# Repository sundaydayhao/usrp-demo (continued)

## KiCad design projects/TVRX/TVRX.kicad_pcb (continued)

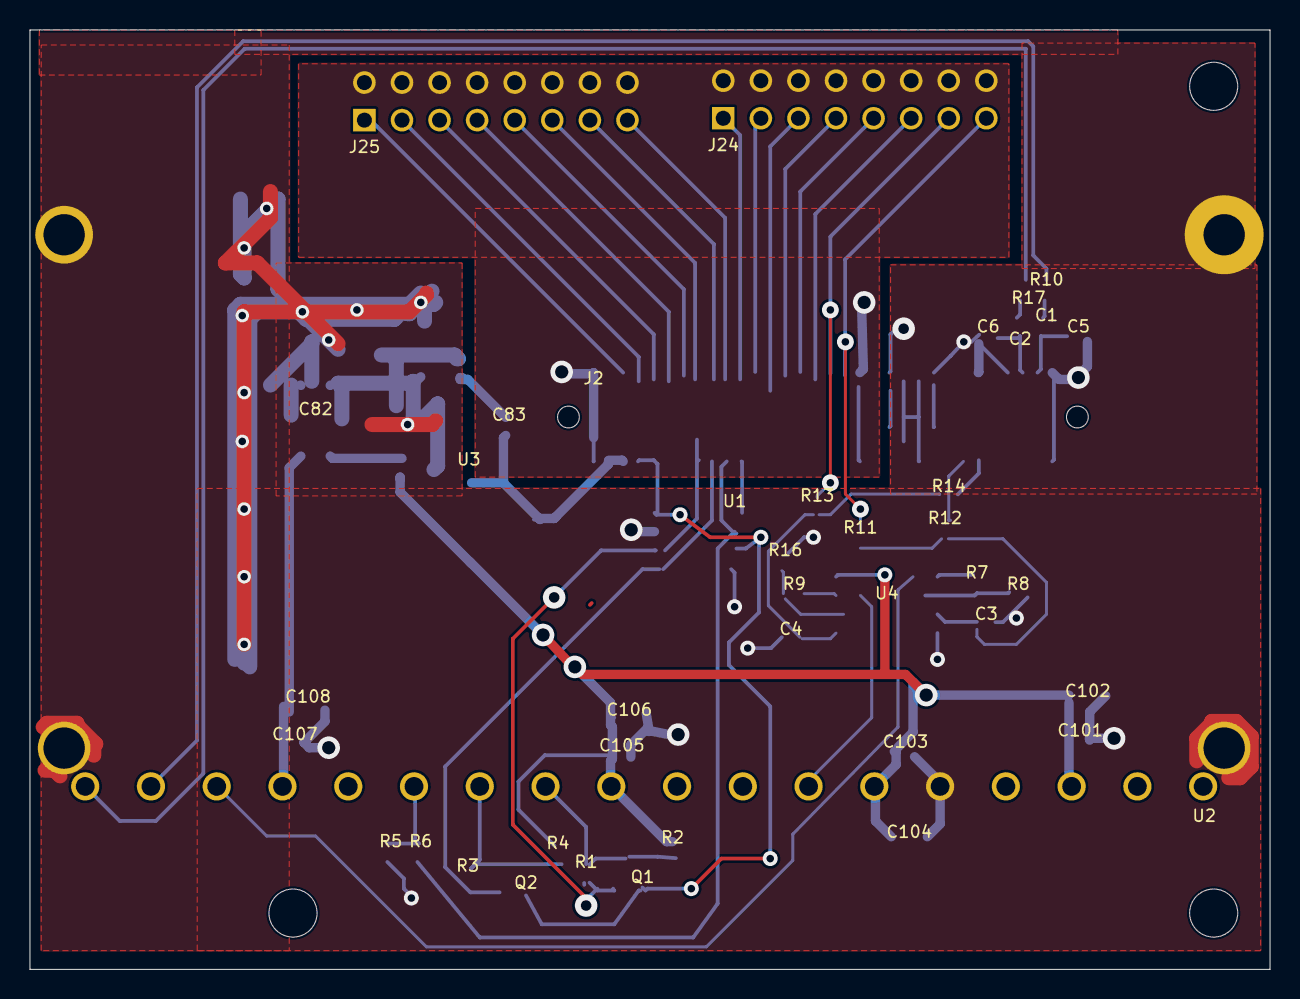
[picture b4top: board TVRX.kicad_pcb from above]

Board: 4 copper layers, 83.8 x 63.5 mm, 44 parts (0 on the bottom side), 43 nets.

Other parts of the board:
H1, H2, H3: NPTH

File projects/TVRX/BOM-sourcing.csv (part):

Reference,Value,Footprint,Manufacturer,MPN,LCSC,Sourcing_status,Specification,Source_value,Evidence,Approved_brands,Sourcing_policy
C1,.1uF,USRP:C1,候选：Murata / TDK / Samsung Electro-Mechanics / Walsin / FH / EYANG,,,规格选型，待锁定料号,按项目焊盘尺寸；RF/匹配/PLL环路优先 C0G；去耦 X7R；耐压 >=16 V；保留原容差,.1uF,,Murata / TDK / Samsung Electro-Mechanics / Walsin / FH / EYANG,国产与国际品牌均可；满足参数后比较含税到手价、起订量、库存和交期；换料须复核封装及电气指标
C2,.1uF,USRP:C2,候选：Murata / TDK / Samsung Electro-Mechanics / Walsin / FH / EYANG,,,规格选型，待锁定料号,按项目焊盘尺寸；RF/匹配/PLL环路优先 C0G；去耦 X7R；耐压 >=16 V；保留原容差,.1uF,,Murata / TDK / Samsung Electro-Mechanics / Walsin / FH / EYANG,国产与国际品牌均可；满足参数后比较含税到手价、起订量、库存和交期；换料须复核封装及电气指标
C3,.1uF,USRP:C3,候选：Murata / TDK / Samsung Electro-Mechanics / Walsin / FH / EYANG,,,规格选型，待锁定料号,按项目焊盘尺寸；RF/匹配/PLL环路优先 C0G；去耦 X7R；耐压 >=16 V；保留原容差,.1uF,,Murata / TDK / Samsung Electro-Mechanics / Walsin / FH / EYANG,国产与国际品牌均可；满足参数后比较含税到手价、起订量、库存和交期；换料须复核封装及电气指标
C4,.1uF,USRP:C4,候选：Murata / TDK / Samsung Electro-Mechanics / Walsin / FH / EYANG,,,规格选型，待锁定料号,按项目焊盘尺寸；RF/匹配/PLL环路优先 C0G；去耦 X7R；耐压 >=16 V；保留原容差,.1uF,,Murata / TDK / Samsung Electro-Mechanics / Walsin / FH / EYANG,国产与国际品牌均可；满足参数后比较含税到手价、起订量、库存和交期；换料须复核封装及电气指标
C5,10pF,USRP:C5,FH 风华高科,0603CG100J500NT,C91367,已核对目录料号，0603 时采用,0603; 10 pF; C0G; 50 V; +/-5%,10pF,https://www.lcsc.com/product-detail/C91367.html,Murata / TDK / Samsung Electro-Mechanics / Walsin / FH / EYANG,国产与国际品牌均可；满足参数后比较含税到手价、起订量、库存和交期；换料须复核封装及电气指标
C6,10pF,USRP:C6,FH 风华高科,0603CG100J500NT,C91367,已核对目录料号，0603 时采用,0603; 10 pF; C0G; 50 V; +/-5%,10pF,https://www.lcsc.com/product-detail/C91367.html,Murata / TDK / Samsung Electro-Mechanics / Walsin / FH / EYANG,国产与国际品牌均可；满足参数后比较含税到手价、起订量、库存和交期；换料须复核封装及电气指标
C82,22uF,USRP:C82,候选：Murata / TDK / Samsung Electro-Mechanics / Walsin / FH / EYANG,,,规格选型，待锁定料号,按项目焊盘尺寸；RF/匹配/PLL环路优先 C0G；去耦 X7R；耐压 >=16 V；保留原容差,22uF,,Murata / TDK / Samsung Electro-Mechanics / Walsin / FH / EYANG,国产与国际品牌均可；满足参数后比较含税到手价、起订量、库存和交期；换料须复核封装及电气指标
C83,.1uF,USRP:C83,候选：Murata / TDK / Samsung Electro-Mechanics / Walsin / FH / EYANG,,,规格选型，待锁定料号,按项目焊盘尺寸；RF/匹配/PLL环路优先 C0G；去耦 X7R；耐压 >=16 V；保留原容差,.1uF,,Murata / TDK / Samsung Electro-Mechanics / Walsin / FH / EYANG,国产与国际品牌均可；满足参数后比较含税到手价、起订量、库存和交期；换料须复核封装及电气指标
C101,470pF,USRP:C101,候选：Murata / TDK / Samsung Electro-Mechanics / Walsin / FH / EYANG,,,规格选型，待锁定料号,按项目焊盘尺寸；RF/匹配/PLL环路优先 C0G；去耦 X7R；耐压 >=16 V；保留原容差,470pF,,Murata / TDK / Samsung Electro-Mechanics / Walsin / FH / EYANG,国产与国际品牌均可；满足参数后比较含税到手价、起订量、库存和交期；换料须复核封装及电气指标
C102,4.7uF,USRP:C102,候选：Murata / TDK / Samsung Electro-Mechanics / Walsin / FH / EYANG,,,规格选型，待锁定料号,按项目焊盘尺寸；RF/匹配/PLL环路优先 C0G；去耦 X7R；耐压 >=16 V；保留原容差,4.7uF,,Murata / TDK / Samsung Electro-Mechanics / Walsin / FH / EYANG,国产与国际品牌均可；满足参数后比较含税到手价、起订量、库存和交期；换料须复核封装及电气指标
C103,470pF,USRP:C103,候选：Murata / TDK / Samsung Electro-Mechanics / Walsin / FH / EYANG,,,规格选型，待锁定料号,按项目焊盘尺寸；RF/匹配/PLL环路优先 C0G；去耦 X7R；耐压 >=16 V；保留原容差,470pF,,Murata / TDK / Samsung Electro-Mechanics / Walsin / FH / EYANG,国产与国际品牌均可；满足参数后比较含税到手价、起订量、库存和交期；换料须复核封装及电气指标
C104,4.7uF,USRP:C104,候选：Murata / TDK / Samsung Electro-Mechanics / Walsin / FH / EYANG,,,规格选型，待锁定料号,按项目焊盘尺寸；RF/匹配/PLL环路优先 C0G；去耦 X7R；耐压 >=16 V；保留原容差,4.7uF,,Murata / TDK / Samsung Electro-Mechanics / Walsin / FH / EYANG,国产与国际品牌均可；满足参数后比较含税到手价、起订量、库存和交期；换料须复核封装及电气指标
C105,470pF,USRP:C105,候选：Murata / TDK / Samsung Electro-Mechanics / Walsin / FH / EYANG,,,规格选型，待锁定料号,按项目焊盘尺寸；RF/匹配/PLL环路优先 C0G；去耦 X7R；耐压 >=16 V；保留原容差,470pF,,Murata / TDK / Samsung Electro-Mechanics / Walsin / FH / EYANG,国产与国际品牌均可；满足参数后比较含税到手价、起订量、库存和交期；换料须复核封装及电气指标
C106,4.7uF,USRP:C106,候选：Murata / TDK / Samsung Electro-Mechanics / Walsin / FH / EYANG,,,规格选型，待锁定料号,按项目焊盘尺寸；RF/匹配/PLL环路优先 C0G；去耦 X7R；耐压 >=16 V；保留原容差,4.7uF,,Murata / TDK / Samsung Electro-Mechanics / Walsin / FH / EYANG,国产与国际品牌均可；满足参数后比较含税到手价、起订量、库存和交期；换料须复核封装及电气指标
C107,470pF,USRP:C107,候选：Murata / TDK / Samsung Electro-Mechanics / Walsin / FH / EYANG,,,规格选型，待锁定料号,按项目焊盘尺寸；RF/匹配/PLL环路优先 C0G；去耦 X7R；耐压 >=16 V；保留原容差,470pF,,Murata / TDK / Samsung Electro-Mechanics / Walsin / FH / EYANG,国产与国际品牌均可；满足参数后比较含税到手价、起订量、库存和交期；换料须复核封装及电气指标
C108,4.7uF,USRP:C108,候选：Murata / TDK / Samsung Electro-Mechanics / Walsin / FH / EYANG,,,规格选型，待锁定料号,按项目焊盘尺寸；RF/匹配/PLL环路优先 C0G；去耦 X7R；耐压 >=16 V；保留原容差,4.7uF,,Murata / TDK / Samsung Electro-Mechanics / Walsin / FH / EYANG,国产与国际品牌均可；满足参数后比较含税到手价、起订量、库存和交期；换料须复核封装及电气指标
J2,PMC64,USRP:J2,,,,规格选型，待锁定料号,按工程封装和 USRP1 接口核对插合方向、针脚与高度,PMC64,,,
J24,HEADER16,USRP:J24,,,,规格选型，待锁定料号,按工程封装和 USRP1 接口核对插合方向、针脚与高度,HEADER16,,,
J25,HEADER16,USRP:J25,,,,规格选型，待锁定料号,按工程封装和 USRP1 接口核对插合方向、针脚与高度,HEADER16,,,
Q1,NDS355AN,USRP:Q1,,NDS355AN,,保留原功能型号；采购需核对后缀、封装与供应状态,射频/高速/低噪声器件，不作未经验证的国产等效替换,NMOS_TRANSISTOR,,,
Q2,NDS355AN,USRP:Q2,,NDS355AN,,保留原功能型号；采购需核对后缀、封装与供应状态,射频/高速/低噪声器件，不作未经验证的国产等效替换,NMOS_TRANSISTOR,,,
R1,NONE,USRP:R1,,,,DNP 不装,保留调试/选配焊盘,NONE,,,
R2,2.2K,USRP:R2,候选：YAGEO / Vishay / Panasonic / UNI-ROYAL / FH,,,规格选型，待锁定料号,0603; <=1%; >=0.1 W; 按原值采购；反馈/终端电阻需同批次,2.2K,,YAGEO / Vishay / Panasonic / UNI-ROYAL / FH,国产与国际品牌均可；满足参数后比较含税到手价、起订量、库存和交期；换料须复核封装及电气指标
R3,NONE,USRP:R3,,,,DNP 不装,保留调试/选配焊盘,NONE,,,
R4,2.2K,USRP:R4,候选：YAGEO / Vishay / Panasonic / UNI-ROYAL / FH,,,规格选型，待锁定料号,0603; <=1%; >=0.1 W; 按原值采购；反馈/终端电阻需同批次,2.2K,,YAGEO / Vishay / Panasonic / UNI-ROYAL / FH,国产与国际品牌均可；满足参数后比较含税到手价、起订量、库存和交期；换料须复核封装及电气指标
R5,1K,USRP:R5,候选：YAGEO / Vishay / Panasonic / UNI-ROYAL / FH,,,规格选型，待锁定料号,0603; <=1%; >=0.1 W; 按原值采购；反馈/终端电阻需同批次,1K,,YAGEO / Vishay / Panasonic / UNI-ROYAL / FH,国产与国际品牌均可；满足参数后比较含税到手价、起订量、库存和交期；换料须复核封装及电气指标
R6,1.6K,USRP:R6,候选：YAGEO / Vishay / Panasonic / UNI-ROYAL / FH,,,规格选型，待锁定料号,0603; <=1%; >=0.1 W; 按原值采购；反馈/终端电阻需同批次,1.6K,,YAGEO / Vishay / Panasonic / UNI-ROYAL / FH,国产与国际品牌均可；满足参数后比较含税到手价、起订量、库存和交期；换料须复核封装及电气指标
R7,2.2K,USRP:R7,候选：YAGEO / Vishay / Panasonic / UNI-ROYAL / FH,,,规格选型，待锁定料号,0603; <=1%; >=0.1 W; 按原值采购；反馈/终端电阻需同批次,2.2K,,YAGEO / Vishay / Panasonic / UNI-ROYAL / FH,国产与国际品牌均可；满足参数后比较含税到手价、起订量、库存和交期；换料须复核封装及电气指标
R8,10K,USRP:R8,候选：YAGEO / Vishay / Panasonic / UNI-ROYAL / FH,,,规格选型，待锁定料号,0603; <=1%; >=0.1 W; 按原值采购；反馈/终端电阻需同批次,10K,,YAGEO / Vishay / Panasonic / UNI-ROYAL / FH,国产与国际品牌均可；满足参数后比较含税到手价、起订量、库存和交期；换料须复核封装及电气指标
R9,2.2K,USRP:R9,候选：YAGEO / Vishay / Panasonic / UNI-ROYAL / FH,,,规格选型，待锁定料号,0603; <=1%; >=0.1 W; 按原值采购；反馈/终端电阻需同批次,2.2K,,YAGEO / Vishay / Panasonic / UNI-ROYAL / FH,国产与国际品牌均可；满足参数后比较含税到手价、起订量、库存和交期；换料须复核封装及电气指标
R10,0,USRP:R10,UNI-ROYAL 厚声,0603WAF0000T5E,C21189,已核对目录料号,0603; <=1%; >=0.1 W; 按原值采购；反馈/终端电阻需同批次,0,https://www.lcsc.com/product-detail/C21189.html,YAGEO / Vishay / Panasonic / UNI-ROYAL / FH,国产与国际品牌均可；满足参数后比较含税到手价、起订量、库存和交期；换料须复核封装及电气指标
R11,NONE,USRP:R11,,,,DNP 不装,保留调试/选配焊盘,NONE,,,
R12,10K,USRP:R12,候选：YAGEO / Vishay / Panasonic / UNI-ROYAL / FH,,,规格选型，待锁定料号,0603; <=1%; >=0.1 W; 按原值采购；反馈/终端电阻需同批次,10K,,YAGEO / Vishay / Panasonic / UNI-ROYAL / FH,国产与国际品牌均可；满足参数后比较含税到手价、起订量、库存和交期；换料须复核封装及电气指标
R13,NONE,USRP:R13,,,,DNP 不装,保留调试/选配焊盘,NONE,,,
R14,10K,USRP:R14,候选：YAGEO / Vishay / Panasonic / UNI-ROYAL / FH,,,规格选型，待锁定料号,0603; <=1%; >=0.1 W; 按原值采购；反馈/终端电阻需同批次,10K,,YAGEO / Vishay / Panasonic / UNI-ROYAL / FH,国产与国际品牌均可；满足参数后比较含税到手价、起订量、库存和交期；换料须复核封装及电气指标
R16,10K,USRP:R16,候选：YAGEO / Vishay / Panasonic / UNI-ROYAL / FH,,,规格选型，待锁定料号,0603; <=1%; >=0.1 W; 按原值采购；反馈/终端电阻需同批次,10K,,YAGEO / Vishay / Panasonic / UNI-ROYAL / FH,国产与国际品牌均可；满足参数后比较含税到手价、起订量、库存和交期；换料须复核封装及电气指标
R17,0,USRP:R17,UNI-ROYAL 厚声,0603WAF0000T5E,C21189,已核对目录料号,0603; <=1%; >=0.1 W; 按原值采购；反馈/终端电阻需同批次,0,https://www.lcsc.com/product-detail/C21189.html,YAGEO / Vishay / Panasonic / UNI-ROYAL / FH,国产与国际品牌均可；满足参数后比较含税到手价、起订量、库存和交期；换料须复核封装及电气指标
U1,AT24C02,USRP:U1,Microchip,AT24C02C-SSHM-T,C6203,已核对引脚/封装/电压/目录；8-byte页写；待实机写入及识别,"SOIC-8 3.9x4.9 mm, P1.27 mm; 1.7–5.5 V; 2 Kbit (256x8); 8-byte page; WP=0; write <=5 ms; ACK polling; 不跨8字节页边界",24LC025B,https://ww1.microchip.com/downloads/en/DeviceDoc/AT24C01C-AT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,Microchip,按完整MPN和厂家采购，不能仅按AT24C02通用名下单
U2,MT4937DI5,USRP:U2,,MT4937DI5,,保留原功能型号；采购需核对后缀、封装与供应状态,射频/高速/低噪声器件，不作未经验证的国产等效替换,MT4937DI5,,,
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
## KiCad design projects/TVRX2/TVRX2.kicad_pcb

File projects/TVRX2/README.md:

# TVRX2

双 TDA18272 调谐器接收板；需要正确 /M、/S 器件和已编程 CPLD。

使用 KiCad 10.0.5 验证。打开 `TVRX2.kicad_pro`，工程内包含可编辑原理图、PCB、`USRP.kicad_sym`、`USRP.pretty` 和本地库表。多页工程从同名顶层原理图进入。

ERC 错误 0，ERC 警告 14；DRC 错误 0，DRC 警告 0，未连接 0。详见检查报告。

- [采购 BOM](BOM-sourcing.csv)：实际 LCSC 编码仅在已核对型号与封装时填写；空白项仍需选型/询价。
- [预览](preview/)：原理图和 PCB 各铜层图。
- [完整设计说明](../../DESIGN_NOTES.md)：原始资料差异、USRP1 机械接口、RF 匹配、叠层、装配和样板验证限制。
- [检查证据](../../verification/TVRX2/)：ERC、DRC、网表、封装与射频检查记录。

必须连同设计说明审查。TVRX2/WBX 使用焊盘内过孔，应评审塞孔盖铜工艺。PCB 上无源器件位号可在 F.Fab/B.Fab 装配层查看。未进行实物功能或射频指标测试。

## 3D 模型

PCB 和本地封装库已绑定工程内的 `3dmodels/`，无需额外安装模型库。请保留整个工程目录。

- [正反面 3D 预览](preview/3d-views.pdf)
- [模型来源、简化模型与尺寸限制](../../3D_MODELS.md)

PMC 插座是简化外形模型；TVRX 的调谐模块也为简化外形，高度按 15 mm 示意，未包含外接 F 连接器。3D 外形补充没有修改电路、焊盘或 RF 走线。

## 2026-09-14 器件更新

EEPROM 已改为 AT24C02，完整料号 Microchip AT24C02C-SSHM-T（C6203）；编程页长 8 字节，不可跨页写入。原有 SOIC-8 焊盘和 3D 模型沿用。阻容感允许按价格、库存和交期选择国内或国际品牌，具体已选料号及待锁定行见本工程 BOM-sourcing.csv；更新证据见 [器件更新说明](../../COMPONENT_UPDATE.md)。

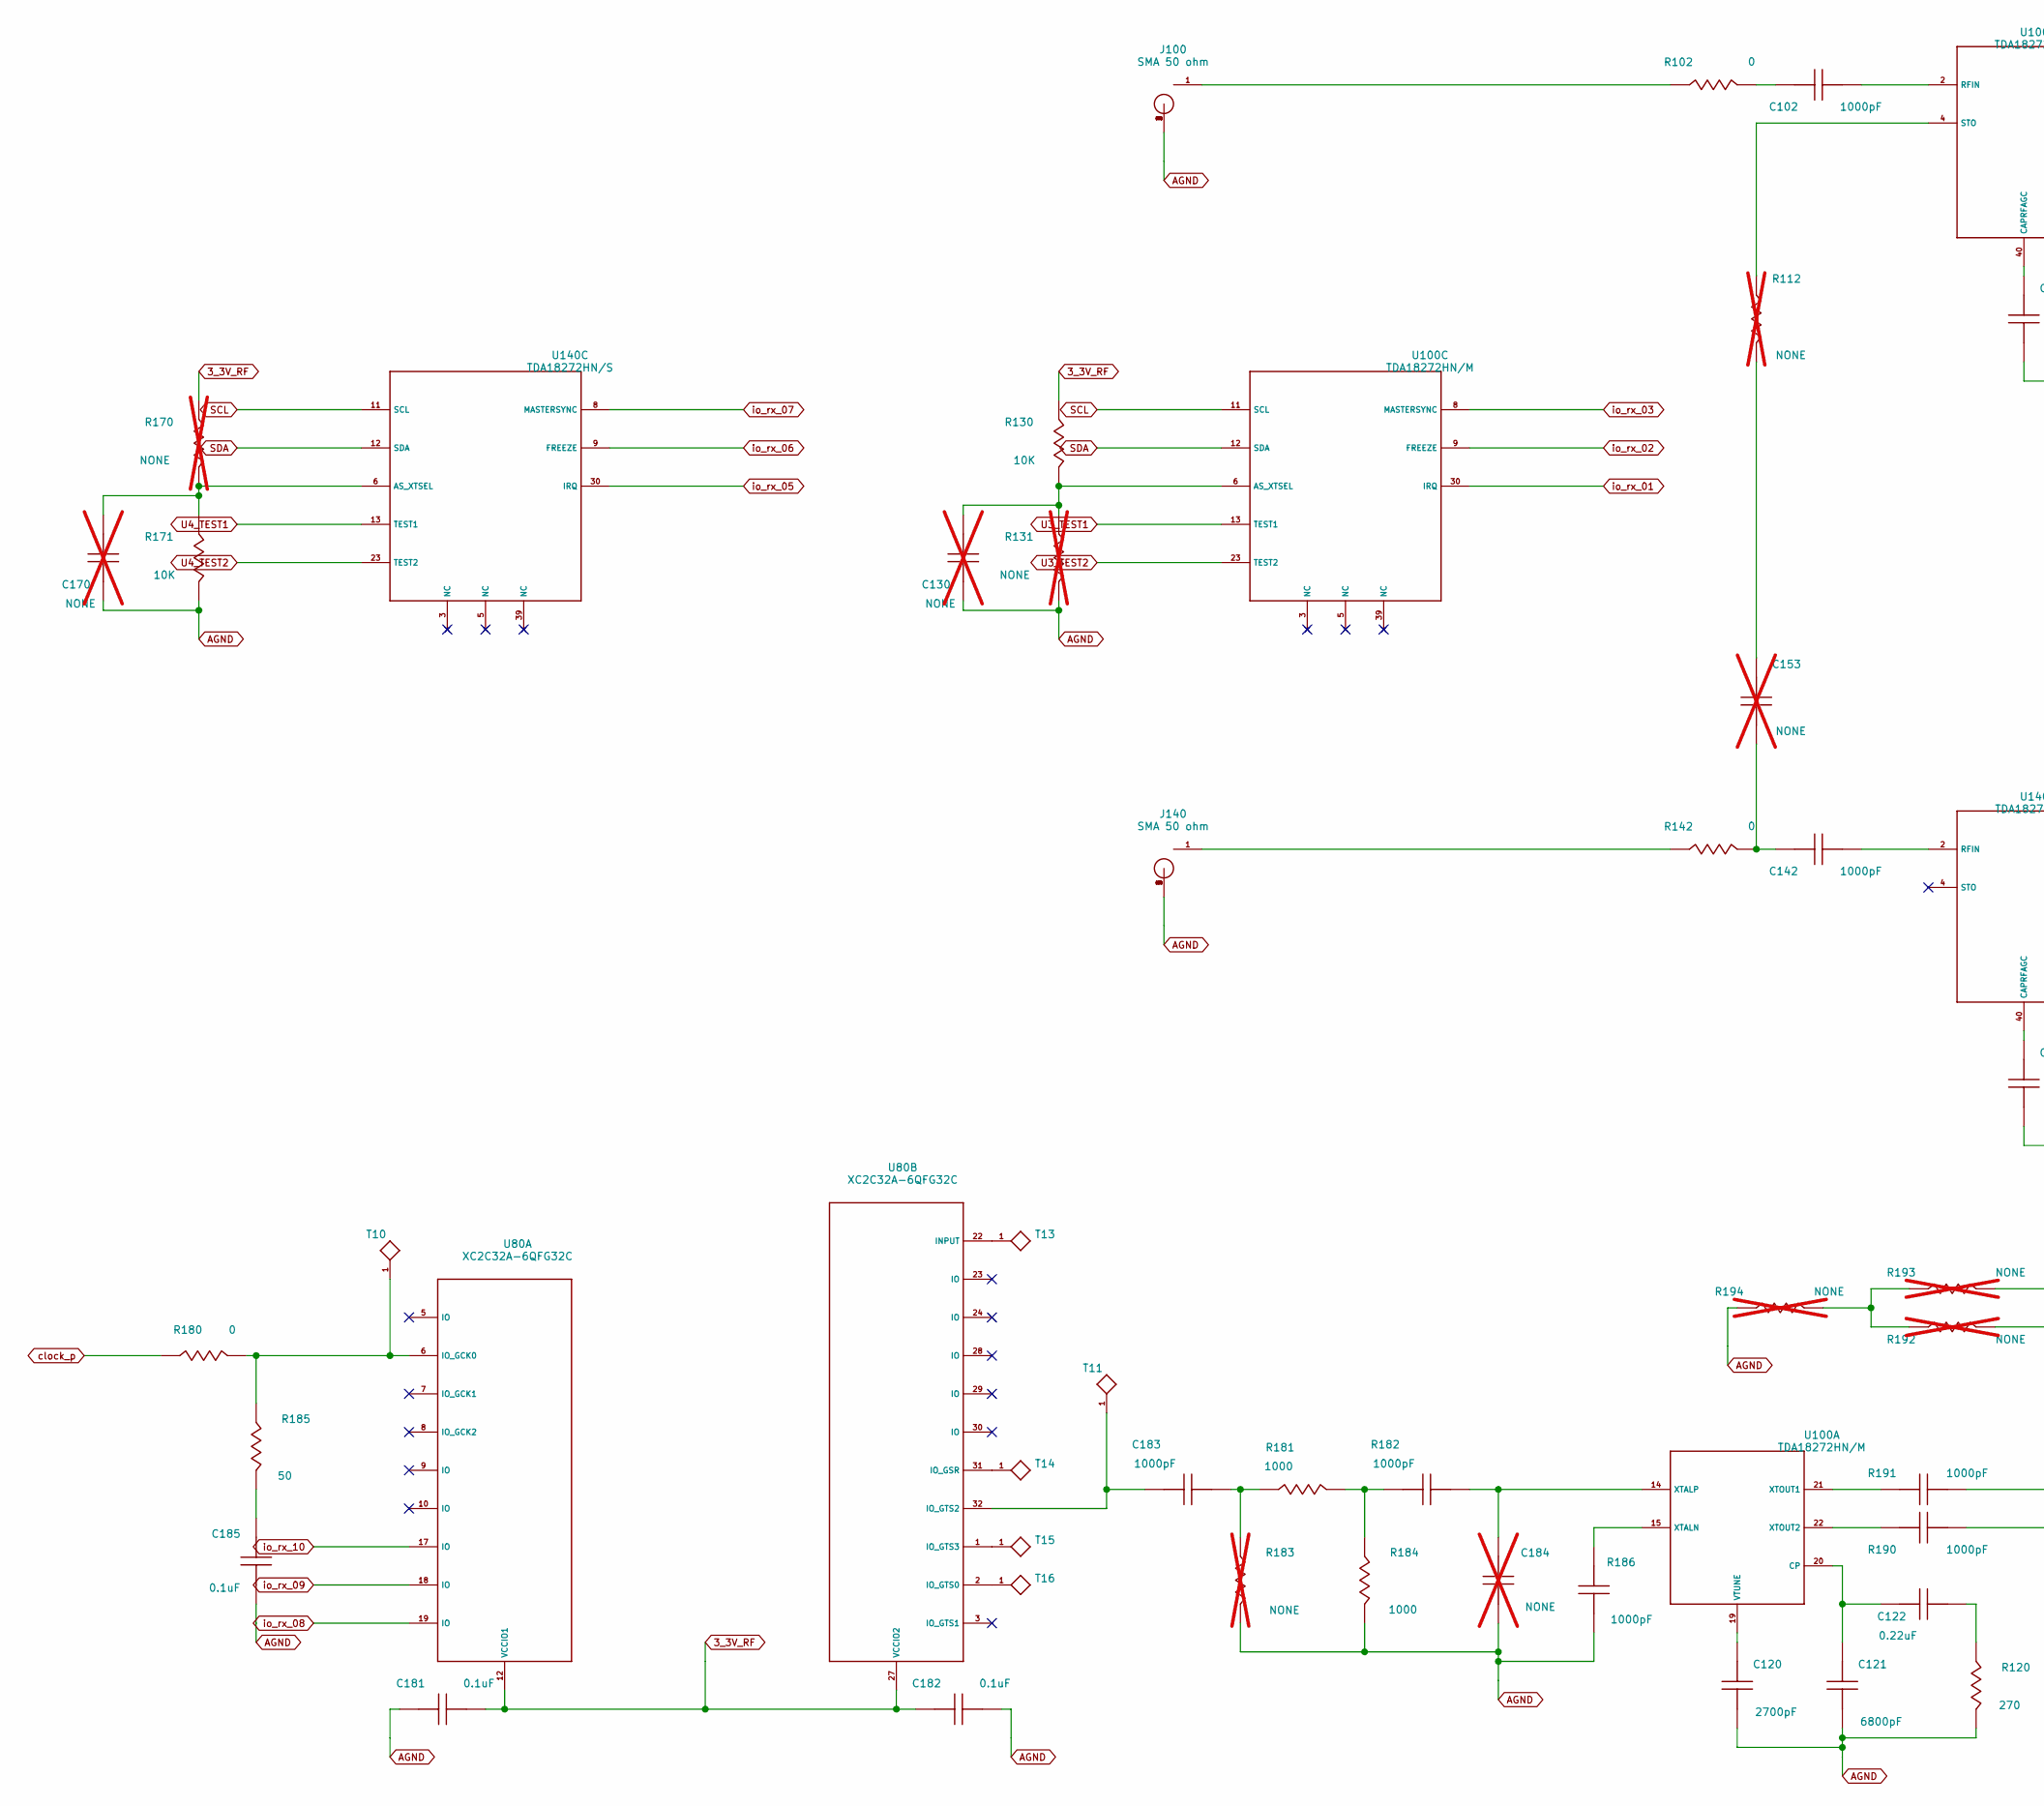
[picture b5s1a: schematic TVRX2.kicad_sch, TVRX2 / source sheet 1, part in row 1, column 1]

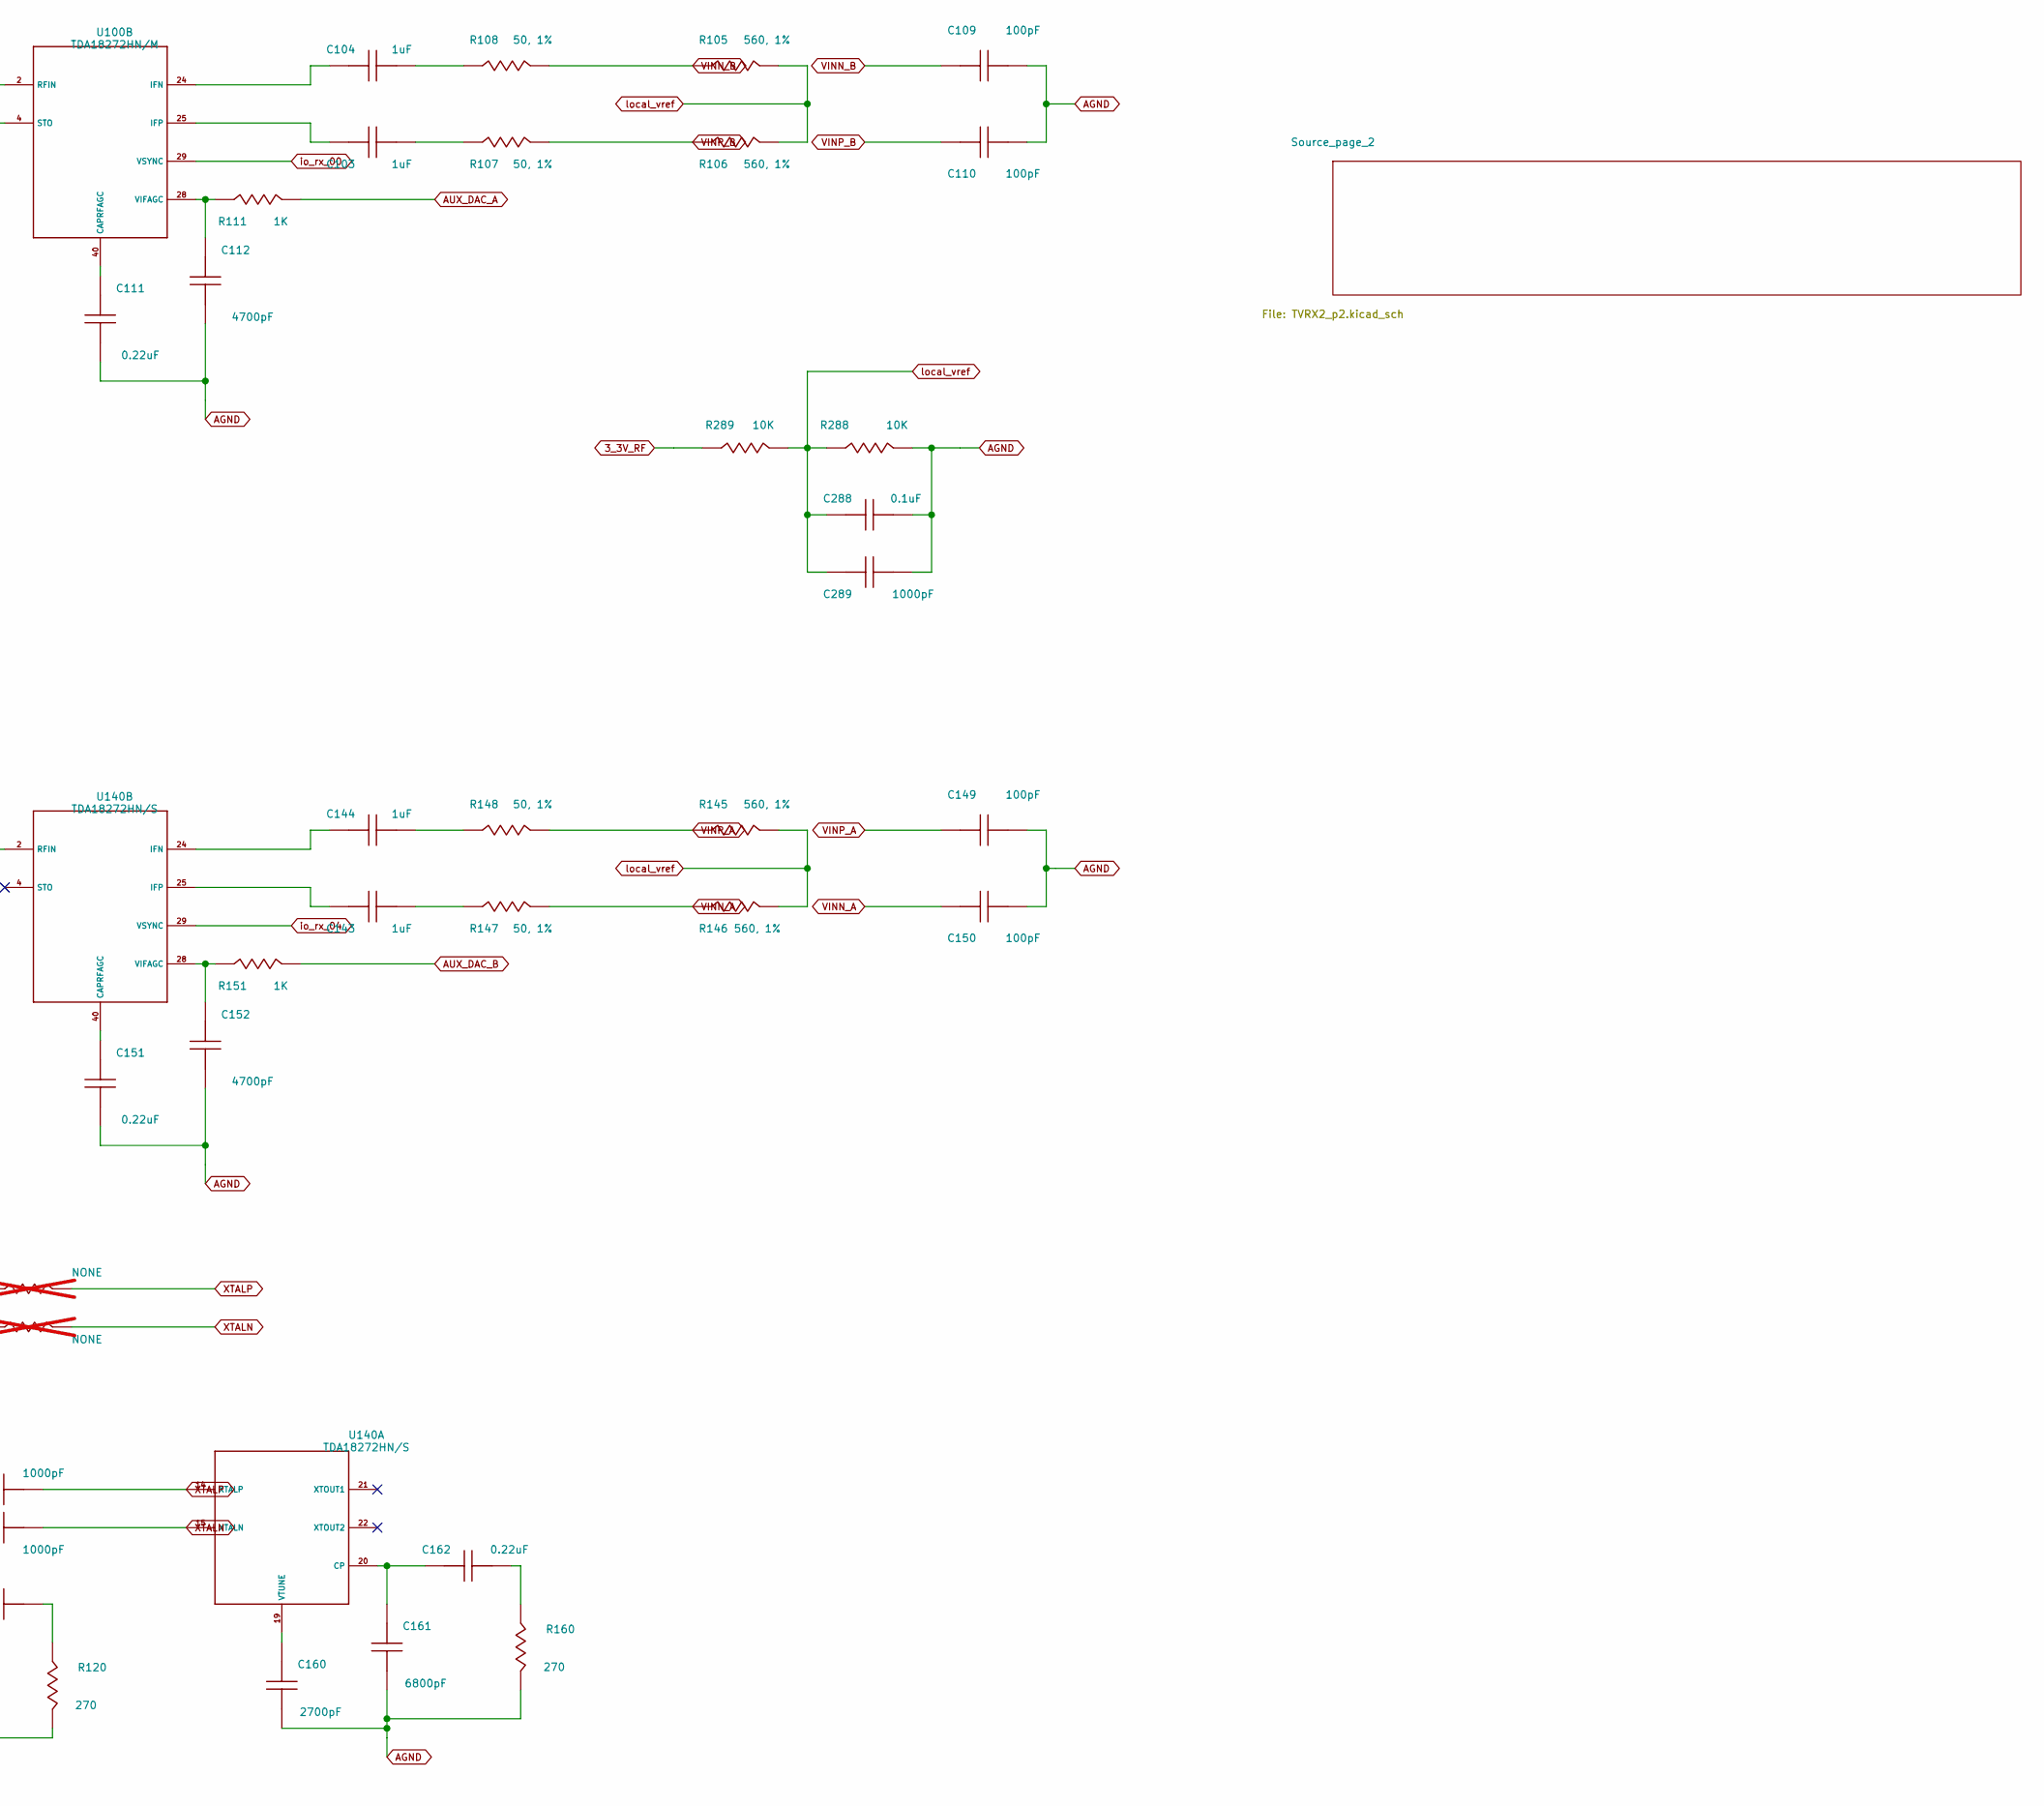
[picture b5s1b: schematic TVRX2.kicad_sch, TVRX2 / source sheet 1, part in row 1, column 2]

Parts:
C102: 1000pF; C102
C103: 1uF; C103
C104: 1uF; C104
C109: 100pF; C109
C110: 100pF; C110
C111: 0.22uF; C111
C112: 4700pF; C112
C120: 2700pF; C120
C121: 6800pF; C121
C122: 0.22uF; C122
C130: NONE; C130; not fitted
C142: 1000pF; C142
C143: 1uF; C143
C144: 1uF; C144
C149: 100pF; C149
C150: 100pF; C150
C151: 0.22uF; C151
C152: 4700pF; C152
C153: NONE; C153; not fitted
C160: 2700pF; C160
C161: 6800pF; C161
C162: 0.22uF; C162
C170: NONE; C170; not fitted
C181: 0.1uF; C181; MPN CL05B104KO5NNNC; LCSC C1525
C182: 0.1uF; C182; MPN CL05B104KO5NNNC; LCSC C1525
C183: 1000pF; C183
C184: NONE; C184; not fitted
C185: 0.1uF; C185
C288: 0.1uF; C288
C289: 1000pF; C289
J100: SMA 50 ohm; J100
J140: SMA 50 ohm; J140
R102: 0; R102
R105: 560, 1%; R105
R106: 560, 1%; R106
R107: 50, 1%; R107
R108: 50, 1%; R108
R111: 1K; R111; MPN RC0402FR-071KL; LCSC C106235
R112: NONE; R112; not fitted
R120: 270; R120
R130: 10K; R130
R131: NONE; R131; not fitted
R142: 0; R142
R145: 560, 1%; R145
R146: 560, 1%; R146
R147: 50, 1%; R147
R148: 50, 1%; R148
R151: 1K; R151; MPN RC0402FR-071KL; LCSC C106235
R160: 270; R160
R170: NONE; R170; not fitted
R171: 10K; R171
R180: 0; R180
R181: 1000; R181
R182: 1000pF; R182
R183: NONE; R183; not fitted
R184: 1000; R184
R185: 50; R185
R186: 1000pF; R186
R190: 1000pF; R190
R191: 1000pF; R191
R192: NONE; R192; not fitted
R193: NONE; R193; not fitted
R194: NONE; R194; not fitted
R288: 10K; R288
R289: 10K; R289
T10: TestPoint; T10
T11: TestPoint; T11
T13: TestPoint; T13
T14: TestPoint; T14
T15: TestPoint; T15
T16: TestPoint; T16
U80: XC2C32A-6QFG32C; U80; MPN XC2C32A-6QFG32C
U100: TDA18272HN/M; U100; MPN TDA18272HN/M
U140: TDA18272HN/S; U140; MPN TDA18272HN/S

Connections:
3_3V_RF: C181.2, C182.1, R130.1, R170.1, R289.1, U80.12 (VCCIO1), U80.27 (VCCIO2); also elsewhere on the board
AGND: C109.2, C110.2, C111.2, C112.2, C120.2, C121.2, C130.2, C149.2, C150.2, C151.2, C152.2, C160.2, C161.2, C170.2, C181.1, C182.2, C184.2, C185.2, C288.2, C289.2, J100.2, J100.3, J100.4, J100.5, J140.2, J140.3, J140.4, J140.5, R120.2, R131.2, R160.2, R171.2, R183.2, R184.2, R186.2, R194.1, R288.2; also elsewhere on the board
AUX_DAC_A: R111.2; also elsewhere on the board
AUX_DAC_B: R151.2; also elsewhere on the board
unnamed: C102.1, R102.2
unnamed: C103.2, R107.1
unnamed: C104.2, R108.1
unnamed: C122.2, R120.1
unnamed: C142.1, C153.2, R142.2
unnamed: C143.2, R147.1
unnamed: C144.2, R148.1
unnamed: C153.1, R112.2
unnamed: C162.2, R160.1
unnamed: C183.2, R181.1, R183.1
unnamed: C185.1, R185.2
unnamed: J100.1, R102.1
unnamed: J140.1, R142.1
unnamed: R181.2, R182.1, R184.1
unnamed: R192.1, R193.1, R194.2
unnamed: R180.2, R185.1, T10.1, U80.6 (IO_GCK0)
unnamed: T13.1, U80.22 (INPUT)
unnamed: T14.1, U80.31 (IO_GSR)
unnamed: T16.1, U80.2 (IO_GTS0)
unnamed: C183.1, T11.1, U80.32 (IO_GTS2)
unnamed: T15.1, U80.1 (IO_GTS3)
unnamed: C121.1, C122.1, U100.20 (CP)
unnamed: C120.1, U100.19 (VTUNE)
unnamed: R186.1, U100.15 (XTALN)
unnamed: C184.1, R182.2, U100.14 (XTALP)
unnamed: R191.1, U100.21 (XTOUT1)
unnamed: R190.1, U100.22 (XTOUT2)
unnamed: C111.1, U100.40 (CAPRFAGC)
unnamed: C104.1, U100.24 (IFN)
unnamed: C103.1, U100.25 (IFP)
unnamed: C102.2, U100.2 (RFIN)
unnamed: R112.1, U100.4 (STO)
unnamed: C112.1, R111.1, U100.28 (VIFAGC)
unnamed: C130.1, R130.2, R131.1, U100.6 (AS_XTSEL)
unnamed: C161.1, C162.1, U140.20 (CP)
unnamed: C160.1, U140.19 (VTUNE)
unnamed: C151.1, U140.40 (CAPRFAGC)
unnamed: C144.1, U140.24 (IFN)
unnamed: C143.1, U140.25 (IFP)
unnamed: C142.2, U140.2 (RFIN)
unnamed: C152.1, R151.1, U140.28 (VIFAGC)
unnamed: C170.1, R170.2, R171.1, U140.6 (AS_XTSEL)
SCL: U100.11 (SCL), U140.11 (SCL); also elsewhere on the board
SDA: U100.12 (SDA), U140.12 (SDA); also elsewhere on the board
U3_TEST1: U100.13 (TEST1); also elsewhere on the board
U3_TEST2: U100.23 (TEST2); also elsewhere on the board
U4_TEST1: U140.13 (TEST1); also elsewhere on the board
U4_TEST2: U140.23 (TEST2); also elsewhere on the board
VINN_A: C150.1, R146.1, R147.2; also elsewhere on the board
VINN_B: C109.1, R105.1, R108.2; also elsewhere on the board
VINP_A: C149.1, R145.1, R148.2; also elsewhere on the board
VINP_B: C110.1, R106.1, R107.2; also elsewhere on the board
XTALN: R190.2, R192.2, U140.15 (XTALN)
XTALP: R191.2, R193.2, U140.14 (XTALP)
clock_p: R180.1; also elsewhere on the board
io_rx_00: U100.29 (VSYNC); also elsewhere on the board
io_rx_01: U100.30 (IRQ); also elsewhere on the board
io_rx_02: U100.9 (FREEZE); also elsewhere on the board
io_rx_03: U100.8 (MASTERSYNC); also elsewhere on the board
io_rx_04: U140.29 (VSYNC); also elsewhere on the board
io_rx_05: U140.30 (IRQ); also elsewhere on the board
io_rx_06: U140.9 (FREEZE); also elsewhere on the board
io_rx_07: U140.8 (MASTERSYNC); also elsewhere on the board
io_rx_08: U80.19 (IO); also elsewhere on the board
io_rx_09: U80.18 (IO); also elsewhere on the board
io_rx_10: U80.17 (IO); also elsewhere on the board
local_vref: C288.1, C289.1, R105.2, R106.2, R145.2, R146.2, R288.1, R289.2
